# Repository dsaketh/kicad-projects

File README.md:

# KiCad PCB Projects

This repository contains my PCB design projects created using KiCad.

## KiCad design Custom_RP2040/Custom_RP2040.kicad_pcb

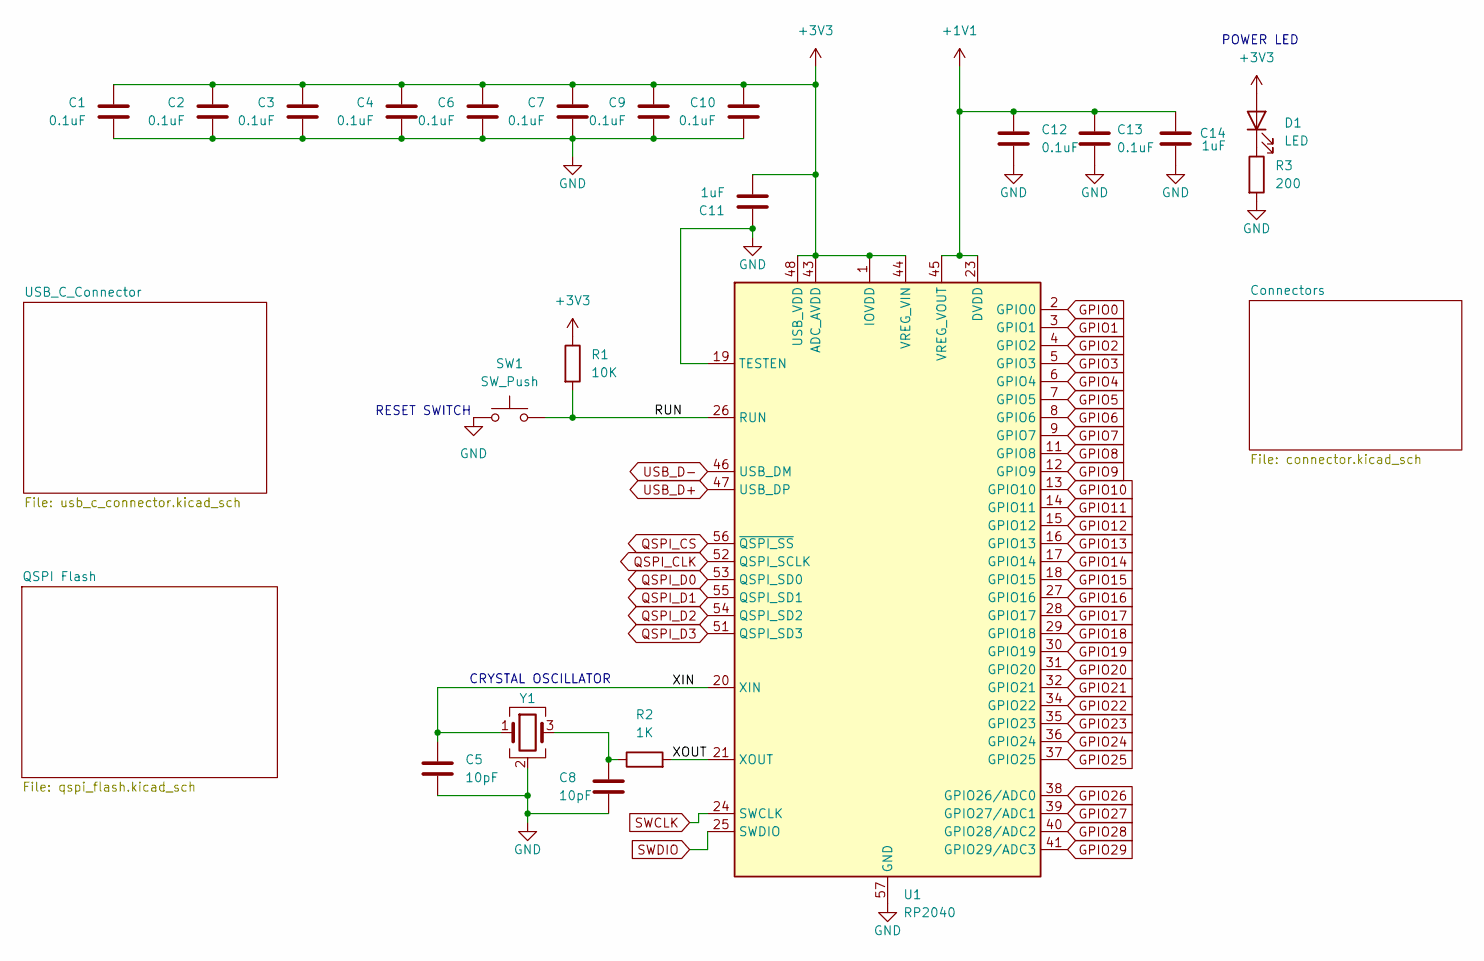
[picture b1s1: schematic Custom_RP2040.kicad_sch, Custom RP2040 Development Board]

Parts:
C1: 0.1uF; C_0603_1608Metric_Pad1.08x0.95mm_HandSolder
C2, C3, C4, C6, C7, C9, C10, C12, C13: 0.1uF; C_0603_1608Metric
C5, C8: 10pF; C_0603_1608Metric
C11, C14: 1uF; C_0603_1608Metric
D1: LED; LED_0603_1608Metric_Pad1.05x0.95mm_HandSolder
R1: 10K; R_0603_1608Metric
R2: 1K; R_0603_1608Metric
R3: 200; R_0603_1608Metric_Pad0.98x0.95mm_HandSolder
SW1: SW_Push; SW_SPST_PTS810
U1: RP2040; QFN-56-1EP_7x7mm_P0.4mm_EP3.2x3.2mm
Y1: Crystal_GND24; Oscillator_SMD_Abracon_ASE-4Pin_3.2x2.5mm

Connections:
+1V1: C12.1, C13.1, C14.2, U1.23 (DVDD), U1.45 (VREG_VOUT), U1.50 (DVDD)
+3V3: C1.1, C2.1, C3.1, C4.1, C6.1, C7.1, C9.1, C10.1, C11.1, D1.2 (A), R1.1, U1.1 (IOVDD), U1.10 (IOVDD), U1.22 (IOVDD), U1.33 (IOVDD), U1.42 (IOVDD), U1.43 (ADC_AVDD), U1.44 (VREG_VIN), U1.48 (USB_VDD), U1.49 (IOVDD); also elsewhere on the board
/RUN: R1.2, SW1.2, U1.26 (RUN)
/XIN: C5.1, U1.20 (XIN), Y1.1
/XOUT: R2.2, U1.21 (XOUT)
GND: C1.2, C2.2, C3.2, C4.2, C5.2, C6.2, C7.2, C8.2, C9.2, C10.2, C11.2, C12.2, C13.2, C14.1, R3.2, SW1.1, U1.19 (TESTEN), U1.57 (GND), Y1.2 (G), Y1.4 (G); also elsewhere on the board
GPIO0: U1.2 (GPIO0); also elsewhere on the board
GPIO1: U1.3 (GPIO1); also elsewhere on the board
GPIO2: U1.4 (GPIO2); also elsewhere on the board
GPIO3: U1.5 (GPIO3); also elsewhere on the board
GPIO4: U1.6 (GPIO4); also elsewhere on the board
GPIO5: U1.7 (GPIO5); also elsewhere on the board
GPIO6: U1.8 (GPIO6); also elsewhere on the board
GPIO7: U1.9 (GPIO7); also elsewhere on the board
GPIO8: U1.11 (GPIO8); also elsewhere on the board
GPIO9: U1.12 (GPIO9); also elsewhere on the board
GPIO10: U1.13 (GPIO10); also elsewhere on the board
GPIO11: U1.14 (GPIO11); also elsewhere on the board
GPIO12: U1.15 (GPIO12); also elsewhere on the board
GPIO13: U1.16 (GPIO13); also elsewhere on the board
GPIO14: U1.17 (GPIO14); also elsewhere on the board
GPIO15: U1.18 (GPIO15); also elsewhere on the board
GPIO16: U1.27 (GPIO16); also elsewhere on the board
GPIO17: U1.28 (GPIO17); also elsewhere on the board
GPIO18: U1.29 (GPIO18); also elsewhere on the board
GPIO19: U1.30 (GPIO19); also elsewhere on the board
GPIO20: U1.31 (GPIO20); also elsewhere on the board
GPIO21: U1.32 (GPIO21); also elsewhere on the board
GPIO22: U1.34 (GPIO22); also elsewhere on the board
GPIO23: U1.35 (GPIO23); also elsewhere on the board
GPIO24: U1.36 (GPIO24); also elsewhere on the board
GPIO25: U1.37 (GPIO25); also elsewhere on the board
GPIO26: U1.38 (GPIO26/ADC0); also elsewhere on the board
GPIO27: U1.39 (GPIO27/ADC1); also elsewhere on the board
GPIO28: U1.40 (GPIO28/ADC2); also elsewhere on the board
GPIO29: U1.41 (GPIO29/ADC3); also elsewhere on the board
unnamed: C8.1, R2.1, Y1.3
unnamed: D1.1 (K), R3.1
QSPI_CLK: U1.52 (QSPI_SCLK); also elsewhere on the board
QSPI_CS: U1.56 (~QSPI_SS); also elsewhere on the board
QSPI_D0: U1.53 (QSPI_SD0); also elsewhere on the board
QSPI_D1: U1.55 (QSPI_SD1); also elsewhere on the board
QSPI_D2: U1.54 (QSPI_SD2); also elsewhere on the board
QSPI_D3: U1.51 (QSPI_SD3); also elsewhere on the board
SWCLK: U1.24 (SWCLK); also elsewhere on the board
SWDIO: U1.25 (SWDIO); also elsewhere on the board
USB_D+: U1.47 (USB_DP); also elsewhere on the board
USB_D-: U1.46 (USB_DM); also elsewhere on the board

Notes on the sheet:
POWER LED
RESET SWITCH
CRYSTAL OSCILLATOR

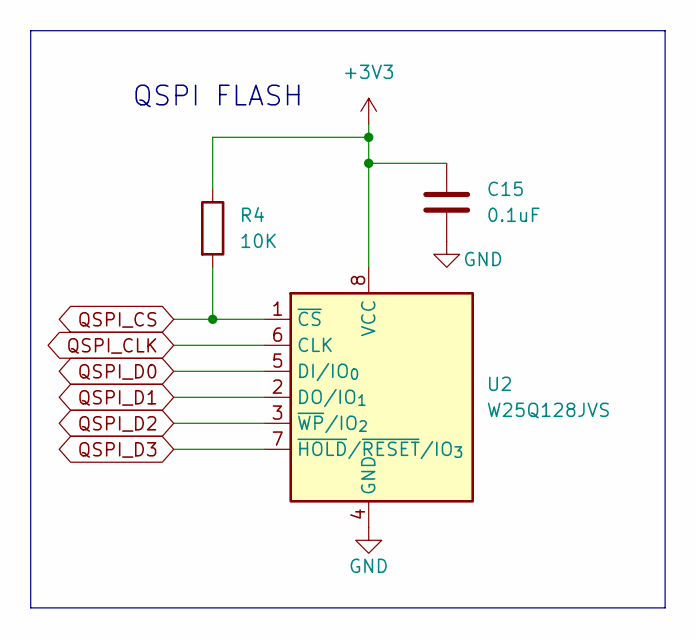
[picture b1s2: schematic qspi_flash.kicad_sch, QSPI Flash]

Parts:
C15: 0.1uF; C_0603_1608Metric
R4: 10K; R_0603_1608Metric
U2: W25Q128JVS; SOIC-8_5.3x5.3mm_P1.27mm

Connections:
+3V3: C15.1, R4.1, U2.8 (VCC); also elsewhere on the board
GND: C15.2, U2.4 (GND); also elsewhere on the board
QSPI_CLK: U2.6 (CLK); also elsewhere on the board
QSPI_CS: R4.2, U2.1 (~CS); also elsewhere on the board
QSPI_D0: U2.5 (DI/IO_{0}); also elsewhere on the board
QSPI_D1: U2.2 (DO/IO_{1}); also elsewhere on the board
QSPI_D2: U2.3 (~WP/IO_{2}); also elsewhere on the board
QSPI_D3: U2.7 (~HOLD/~RESET/IO_{3}); also elsewhere on the board

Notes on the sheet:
QSPI FLASH

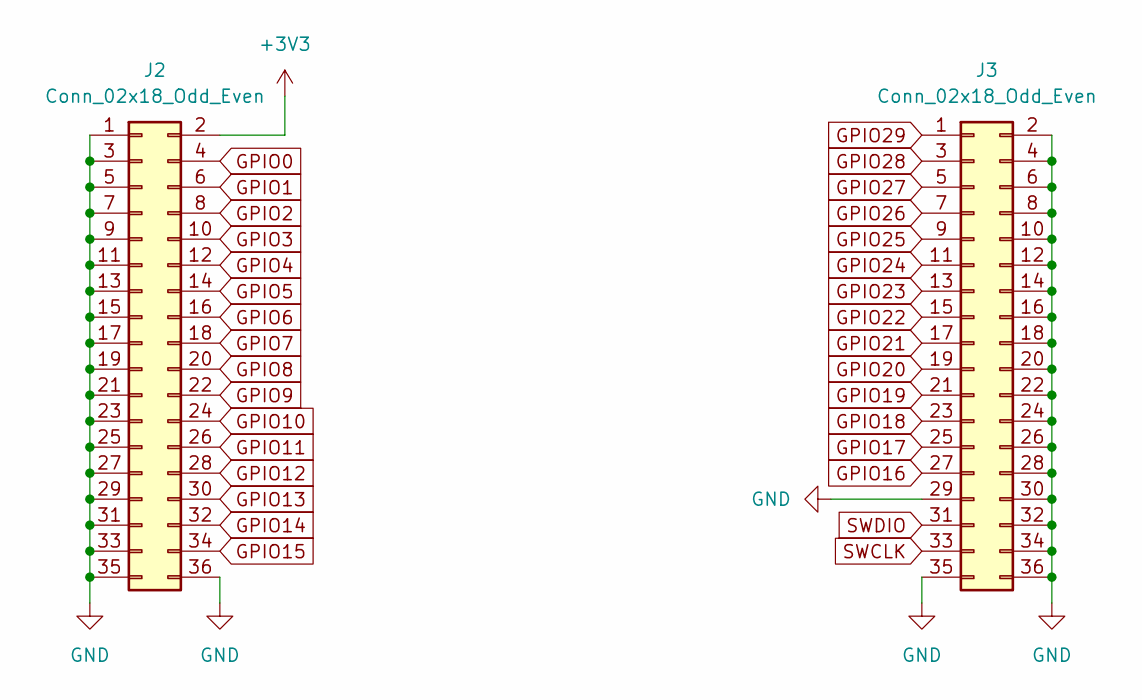
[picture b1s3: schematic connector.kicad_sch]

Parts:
J2, J3: Conn_02x18_Odd_Even; PinHeader_2x18_P2.54mm_Vertical

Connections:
+3V3: J2.2; also elsewhere on the board
GND: J2.1, J2.3, J2.5, J2.7, J2.9, J2.11, J2.13, J2.15, J2.17, J2.19, J2.21, J2.23, J2.25, J2.27, J2.29, J2.31, J2.33, J2.35, J2.36, J3.2, J3.4, J3.6, J3.8, J3.10, J3.12, J3.14, J3.16, J3.18, J3.20, J3.22, J3.24, J3.26, J3.28, J3.29, J3.30, J3.32, J3.34, J3.35, J3.36; also elsewhere on the board
GPIO0: J2.4; also elsewhere on the board
GPIO1: J2.6; also elsewhere on the board
GPIO2: J2.8; also elsewhere on the board
GPIO3: J2.10; also elsewhere on the board
GPIO4: J2.12; also elsewhere on the board
GPIO5: J2.14; also elsewhere on the board
GPIO6: J2.16; also elsewhere on the board
GPIO7: J2.18; also elsewhere on the board
GPIO8: J2.20; also elsewhere on the board
GPIO9: J2.22; also elsewhere on the board
GPIO10: J2.24; also elsewhere on the board
GPIO11: J2.26; also elsewhere on the board
GPIO12: J2.28; also elsewhere on the board
GPIO13: J2.30; also elsewhere on the board
GPIO14: J2.32; also elsewhere on the board
GPIO15: J2.34; also elsewhere on the board
GPIO16: J3.27; also elsewhere on the board
GPIO17: J3.25; also elsewhere on the board
GPIO18: J3.23; also elsewhere on the board
GPIO19: J3.21; also elsewhere on the board
GPIO20: J3.19; also elsewhere on the board
GPIO21: J3.17; also elsewhere on the board
GPIO22: J3.15; also elsewhere on the board
GPIO23: J3.13; also elsewhere on the board
GPIO24: J3.11; also elsewhere on the board
GPIO25: J3.9; also elsewhere on the board
GPIO26: J3.7; also elsewhere on the board
GPIO27: J3.5; also elsewhere on the board
GPIO28: J3.3; also elsewhere on the board
GPIO29: J3.1; also elsewhere on the board
SWCLK: J3.33; also elsewhere on the board
SWDIO: J3.31; also elsewhere on the board

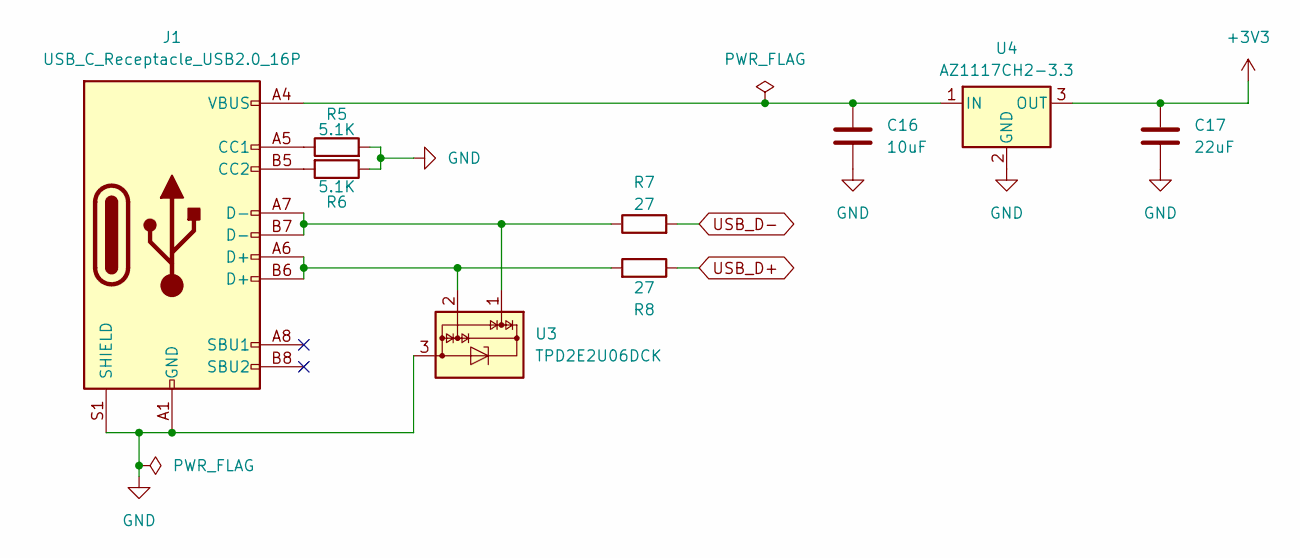
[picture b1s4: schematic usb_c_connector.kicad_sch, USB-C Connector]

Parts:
C16: 10uF; C_0603_1608Metric
C17: 22uF; C_0603_1608Metric
J1: USB_C_Receptacle_USB2.0_16P; USB_C_Receptacle_G-Switch_GT-USB-7010ASV
R5, R6: 5.1K; R_0603_1608Metric
R7, R8: 27; R_0603_1608Metric
U3: TPD2E2U06DCK; SOT-323_SC-70
U4: AZ1117CH2-3.3; SOT-223-3_TabPin2

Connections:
+3V3: C17.1, U4.3 (OUT); also elsewhere on the board
GND: C16.2, C17.2, J1.A1 (GND), J1.A12 (GND), J1.B1 (GND), J1.B12 (GND), J1.S1 (SHIELD), R5.2, R6.1, U3.3, U4.2 (GND); also elsewhere on the board
unnamed: J1.A5 (CC1), R5.1
unnamed: J1.B5 (CC2), R6.2
unnamed: J1.A6 (D+), J1.B6 (D+), R8.2, U3.2
unnamed: J1.A7 (D-), J1.B7 (D-), R7.1, U3.1
unnamed: C16.1, J1.A4 (VBUS), J1.A9 (VBUS), J1.B4 (VBUS), J1.B9 (VBUS), U4.1 (IN)
USB_D+: R8.1; also elsewhere on the board
USB_D-: R7.2; also elsewhere on the board

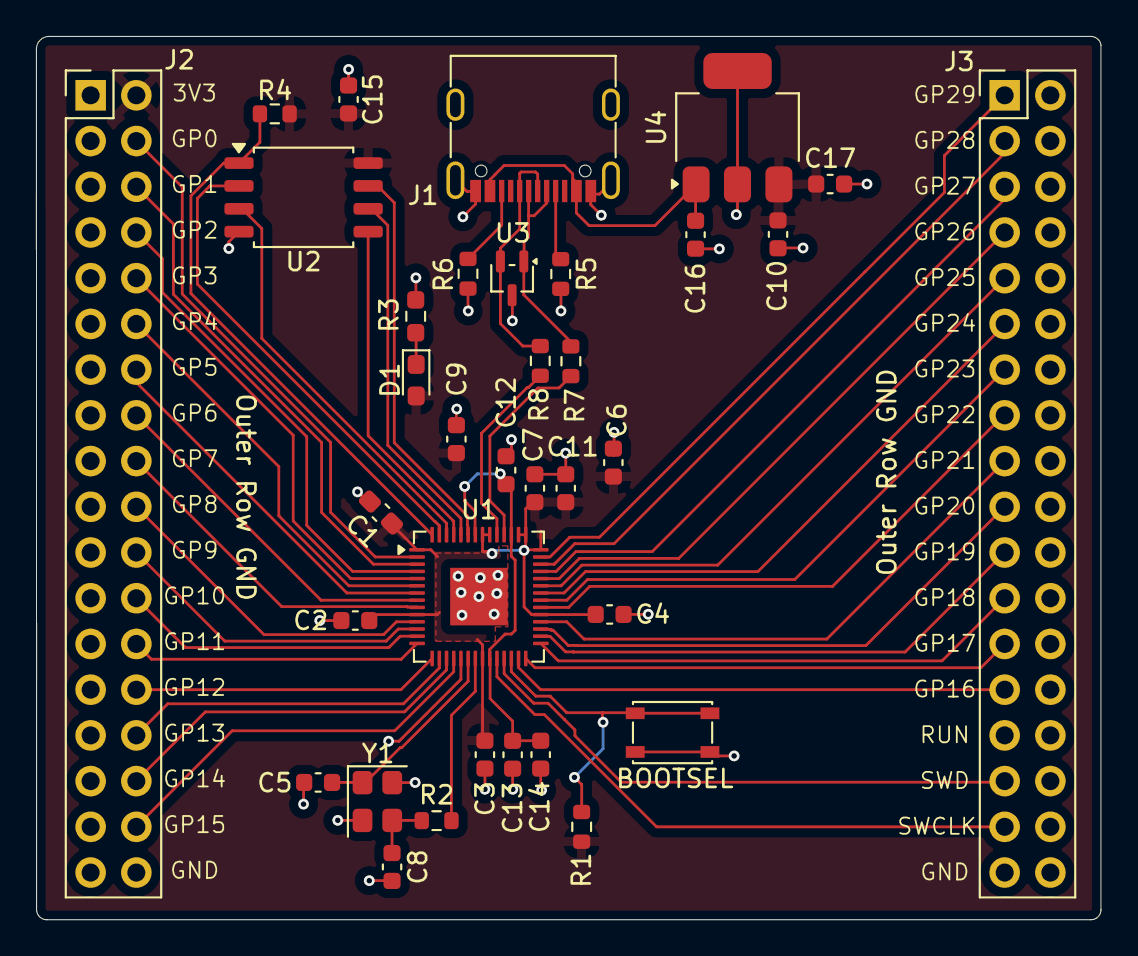
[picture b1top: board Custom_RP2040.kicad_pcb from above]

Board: 2 copper layers, 59.1 x 49.1 mm, 35 parts (0 on the bottom side), 53 nets.

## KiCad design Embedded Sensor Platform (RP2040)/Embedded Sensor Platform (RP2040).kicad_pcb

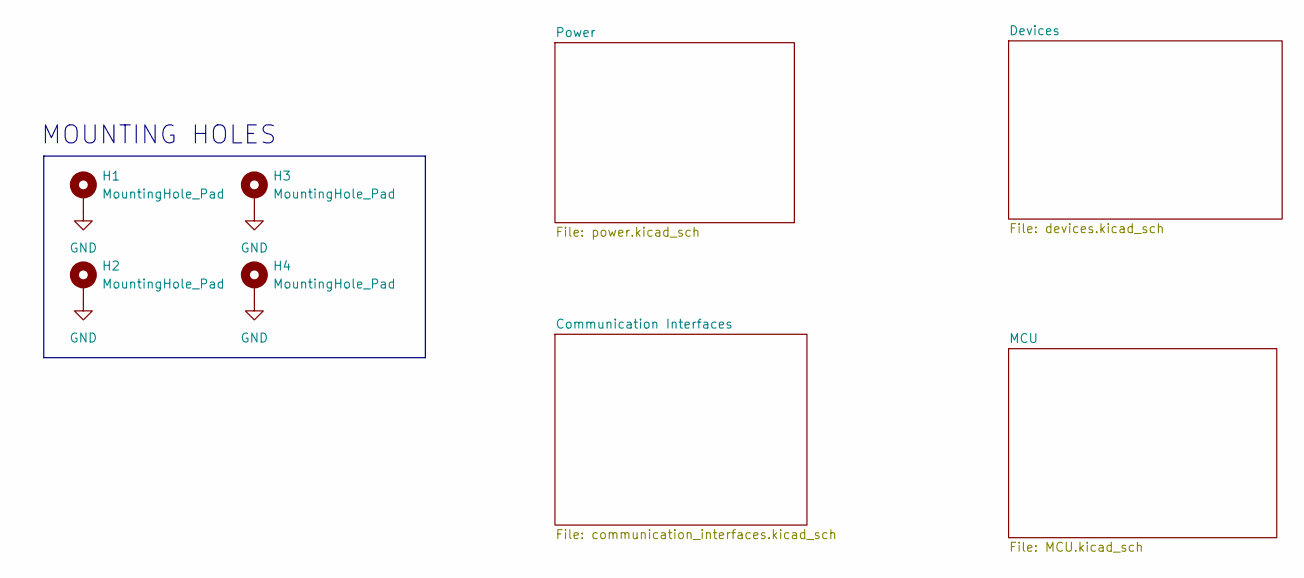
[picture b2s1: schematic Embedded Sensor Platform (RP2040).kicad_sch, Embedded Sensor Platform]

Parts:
H1, H2, H3, H4: MountingHole_Pad; MountingHole_2.2mm_M2_Pad

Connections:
GND: H1.1, H2.1, H3.1, H4.1; also elsewhere on the board

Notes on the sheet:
MOUNTING HOLES

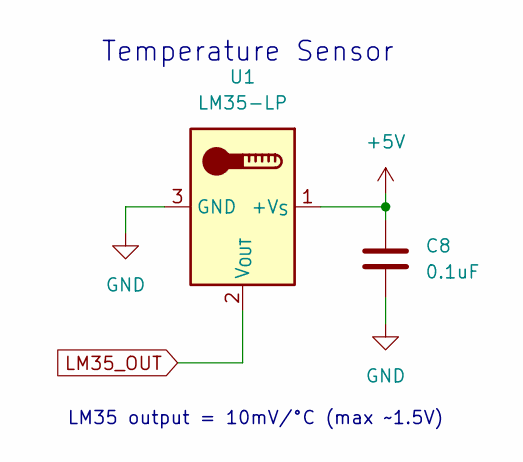
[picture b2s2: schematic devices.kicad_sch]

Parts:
C8: 0.1uF; C_0603_1608Metric_Pad1.08x0.95mm_HandSolder
U1: LM35-LP; TO-92_Inline

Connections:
+5V: C8.1, U1.1 (+V_{S}); also elsewhere on the board
GND: C8.2, U1.3 (GND); also elsewhere on the board
LM35_OUT: U1.2 (V_{OUT}); also elsewhere on the board

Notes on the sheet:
Temperature Sensor
LM35 output = 10mV/°C (max ~1.5V)

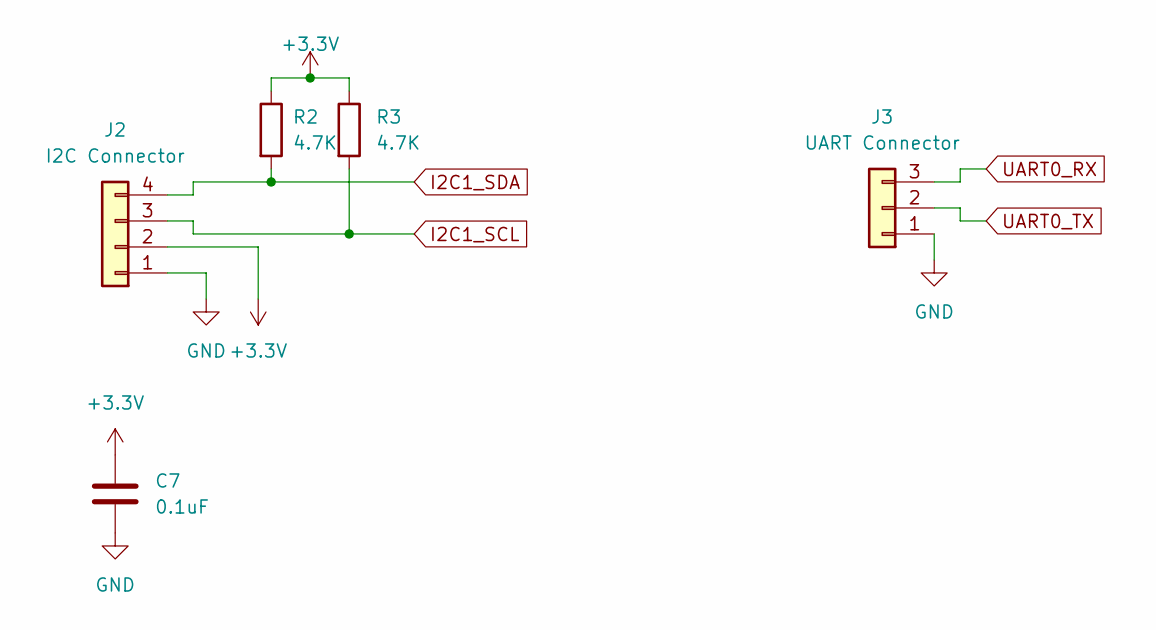
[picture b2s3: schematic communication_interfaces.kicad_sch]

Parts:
C7: 0.1uF; C_0603_1608Metric_Pad1.08x0.95mm_HandSolder
J2: I2C Connector; PinSocket_1x04_P2.00mm_Vertical
J3: UART Connector; PinSocket_1x03_P2.00mm_Vertical
R2, R3: 4.7K; R_0603_1608Metric_Pad0.98x0.95mm_HandSolder

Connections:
+3.3V: C7.1, J2.2, R2.1, R3.1; also elsewhere on the board
GND: C7.2, J2.1, J3.1; also elsewhere on the board
I2C1_SCL: J2.3, R3.2; also elsewhere on the board
I2C1_SDA: J2.4, R2.2; also elsewhere on the board
UART0_RX: J3.3; also elsewhere on the board
UART0_TX: J3.2; also elsewhere on the board

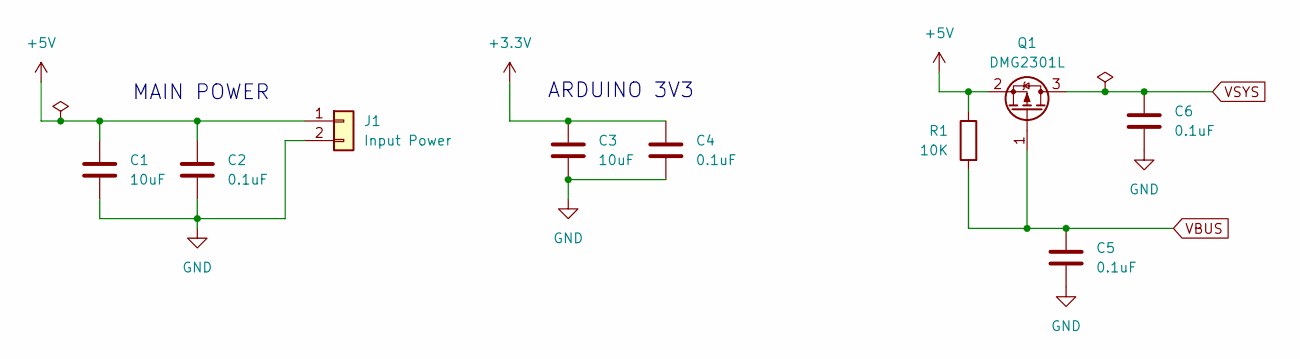
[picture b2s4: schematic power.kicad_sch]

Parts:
C1, C3: 10uF; C_0603_1608Metric_Pad1.08x0.95mm_HandSolder
C2, C4, C5, C6: 0.1uF; C_0603_1608Metric_Pad1.08x0.95mm_HandSolder
J1: Input Power; PinHeader_1x02_P2.00mm_Vertical
Q1: DMG2301L; SOT-23
R1: 10K; R_0603_1608Metric_Pad0.98x0.95mm_HandSolder

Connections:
+3.3V: C3.1, C4.1; also elsewhere on the board
+5V: C1.1, C2.1, J1.1, Q1.2 (S), R1.1; also elsewhere on the board
GND: C1.2, C2.2, C3.2, C4.2, C5.2, C6.2, J1.2; also elsewhere on the board
VBUS: C5.1, Q1.1 (G), R1.2; also elsewhere on the board
VSYS: C6.1, Q1.3 (D); also elsewhere on the board

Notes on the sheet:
ARDUINO 3V3
MAIN POWER

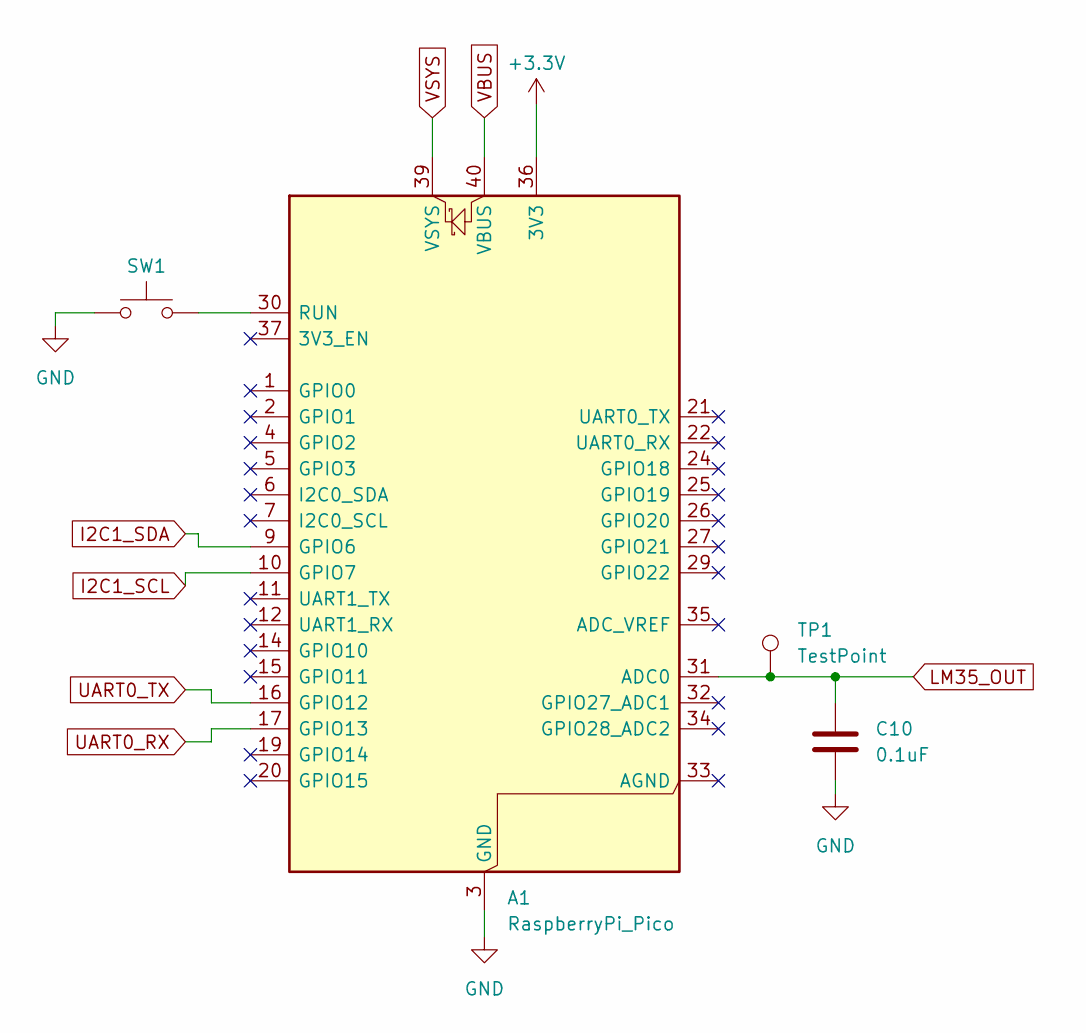
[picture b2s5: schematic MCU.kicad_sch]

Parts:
A1: RaspberryPi_Pico; RaspberryPi_Pico_Common_THT
C10: 0.1uF; C_0603_1608Metric_Pad1.08x0.95mm_HandSolder
SW1: SW_Push; SW_SPST_PTS810
TP1: TestPoint; TestPoint_THTPad_D2.0mm_Drill1.0mm

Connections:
+3.3V: A1.36 (3V3); also elsewhere on the board
GND: A1.3 (GND), A1.8 (GND), A1.13 (GND), A1.18 (GND), A1.23 (GND), A1.28 (GND), A1.38 (GND), C10.2, SW1.1; also elsewhere on the board
I2C1_SCL: A1.10 (GPIO7); also elsewhere on the board
I2C1_SDA: A1.9 (GPIO6); also elsewhere on the board
LM35_OUT: A1.31 (ADC0), C10.1, TP1.1; also elsewhere on the board
unnamed: A1.30 (RUN), SW1.2
UART0_RX: A1.17 (GPIO13); also elsewhere on the board
UART0_TX: A1.16 (GPIO12); also elsewhere on the board
VBUS: A1.40 (VBUS); also elsewhere on the board
VSYS: A1.39 (VSYS); also elsewhere on the board

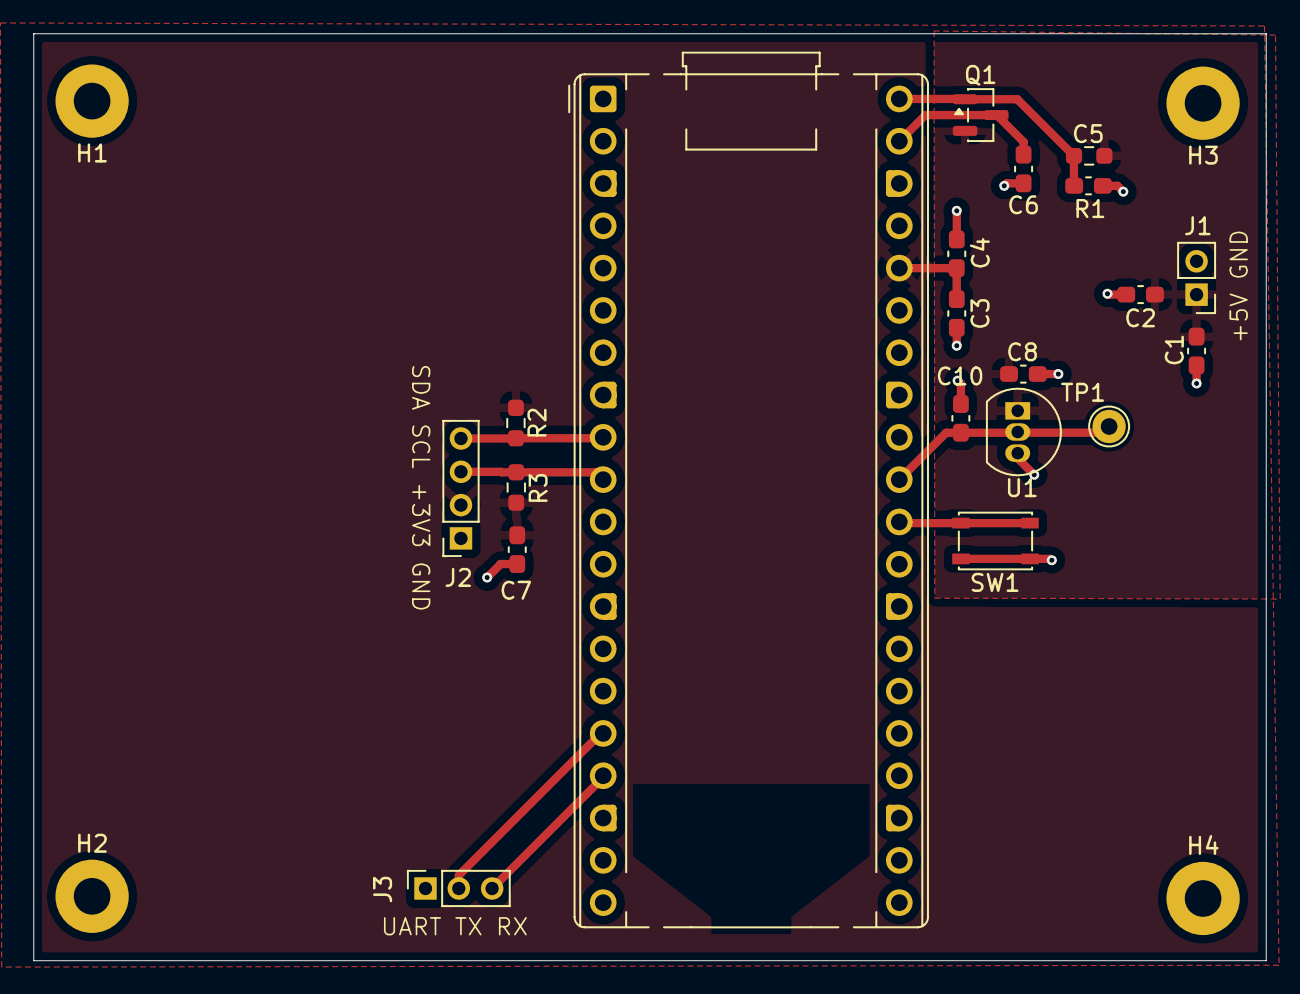
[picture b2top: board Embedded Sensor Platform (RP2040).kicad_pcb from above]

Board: 2 copper layers, 74.0 x 55.7 mm, 24 parts (0 on the bottom side), 11 nets.

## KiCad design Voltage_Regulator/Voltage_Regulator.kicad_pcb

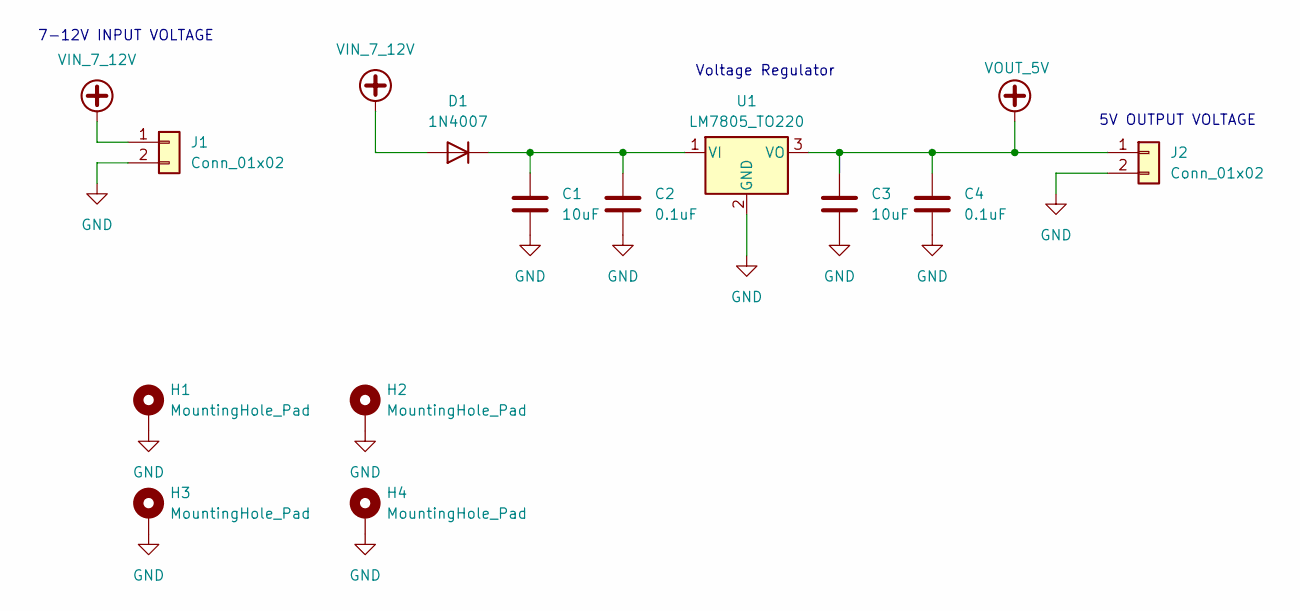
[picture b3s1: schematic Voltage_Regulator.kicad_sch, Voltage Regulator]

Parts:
C1, C3: 10uF; C_0603_1608Metric
C2, C4: 0.1uF; C_0603_1608Metric
D1: 1N4007; D_DO-41_SOD81_P10.16mm_Horizontal
H1, H2, H3, H4: MountingHole_Pad; MountingHole_2.2mm_M2_Pad
J1, J2: Conn_01x02; PinHeader_1x02_P1.00mm_Vertical
U1: LM7805_TO220; TO-220-3_Vertical

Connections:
GND: C1.2, C2.2, C3.2, C4.2, H1.1, H2.1, H3.1, H4.1, J1.2, J2.2, U1.2 (GND)
unnamed: C1.1, C2.1, D1.1 (K), U1.1 (VI)
VIN_7_12V: D1.2 (A), J1.1
VOUT_5V: C3.1, C4.1, J2.1, U1.3 (VO)

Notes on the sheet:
5V OUTPUT VOLTAGE
Voltage Regulator
7-12V INPUT VOLTAGE

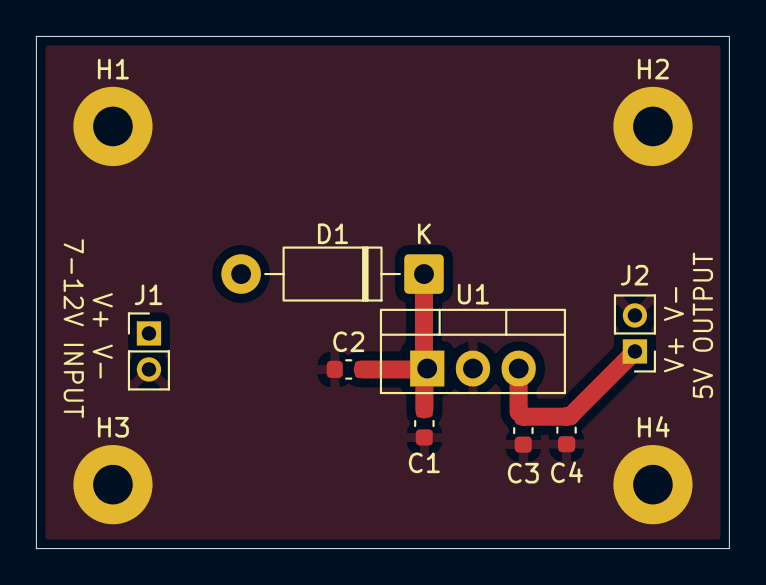
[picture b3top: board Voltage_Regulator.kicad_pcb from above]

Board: 2 copper layers, 38.5 x 28.5 mm, 12 parts (0 on the bottom side), 4 nets.

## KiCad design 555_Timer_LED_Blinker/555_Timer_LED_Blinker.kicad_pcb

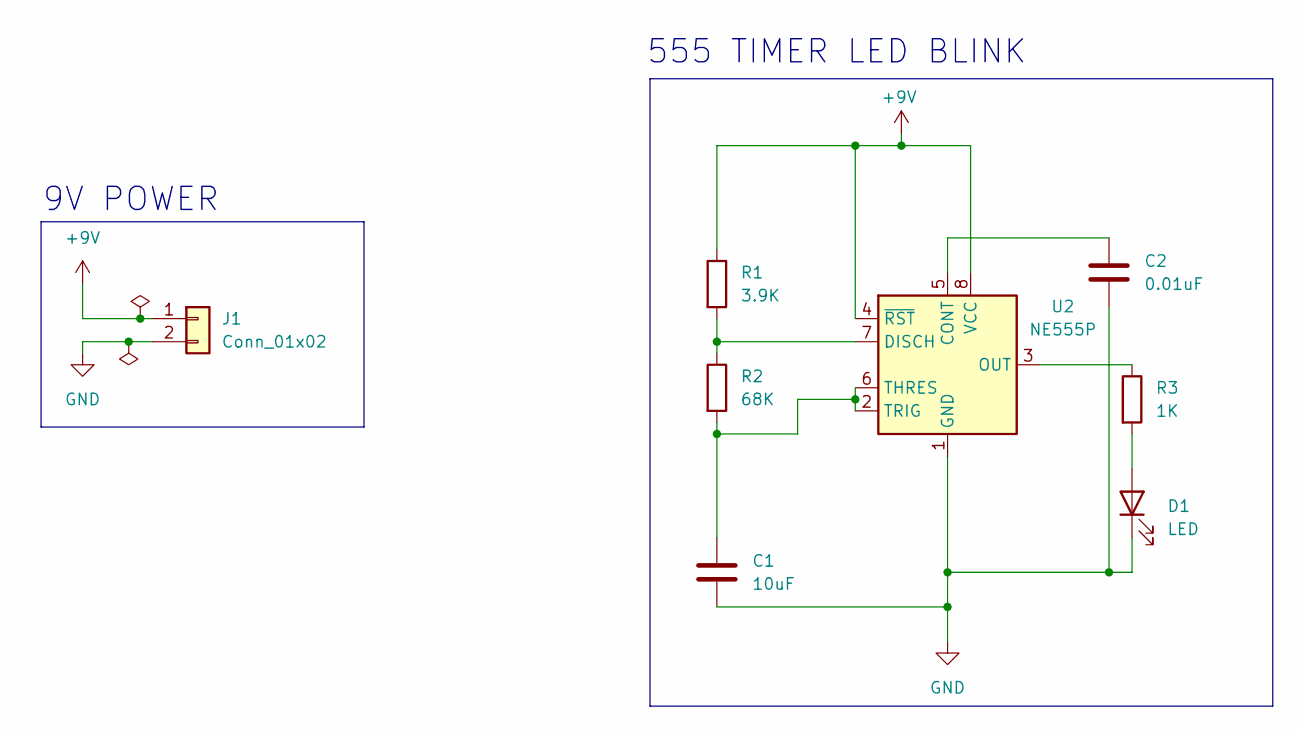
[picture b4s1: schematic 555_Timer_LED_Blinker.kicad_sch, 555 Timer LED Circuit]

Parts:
C1: 10uF; C_0603_1608Metric
C2: 0.01uF; C_0603_1608Metric
D1: LED; LED_D5.0mm
J1: Conn_01x02; PinHeader_1x02_P2.00mm_Vertical
R1: 3.9K; R_0603_1608Metric
R2: 68K; R_0603_1608Metric
R3: 1K; R_0603_1608Metric
U2: NE555P; DIP-8_W7.62mm

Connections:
+9V: J1.1, R1.1, U2.4 (~RST), U2.8 (VCC)
GND: C1.2, C2.2, D1.1 (K), J1.2, U2.1 (GND)
unnamed: D1.2 (A), R3.2
unnamed: C2.1, U2.5 (CONT)
unnamed: R1.2, R2.1, U2.7 (DISCH)
unnamed: R3.1, U2.3 (OUT)
unnamed: C1.1, R2.2, U2.2 (TRIG), U2.6 (THRES)

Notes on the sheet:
555 TIMER LED BLINK
9V POWER

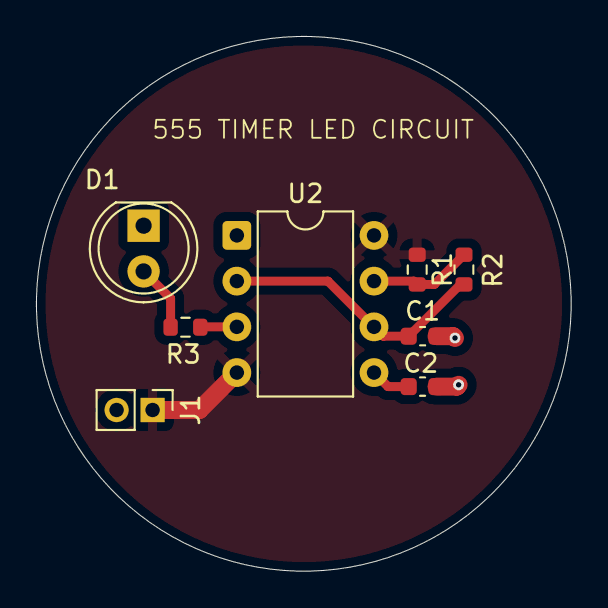
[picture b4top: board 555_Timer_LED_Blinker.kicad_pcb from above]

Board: 2 copper layers, 29.7 x 29.7 mm, 8 parts (0 on the bottom side), 7 nets.

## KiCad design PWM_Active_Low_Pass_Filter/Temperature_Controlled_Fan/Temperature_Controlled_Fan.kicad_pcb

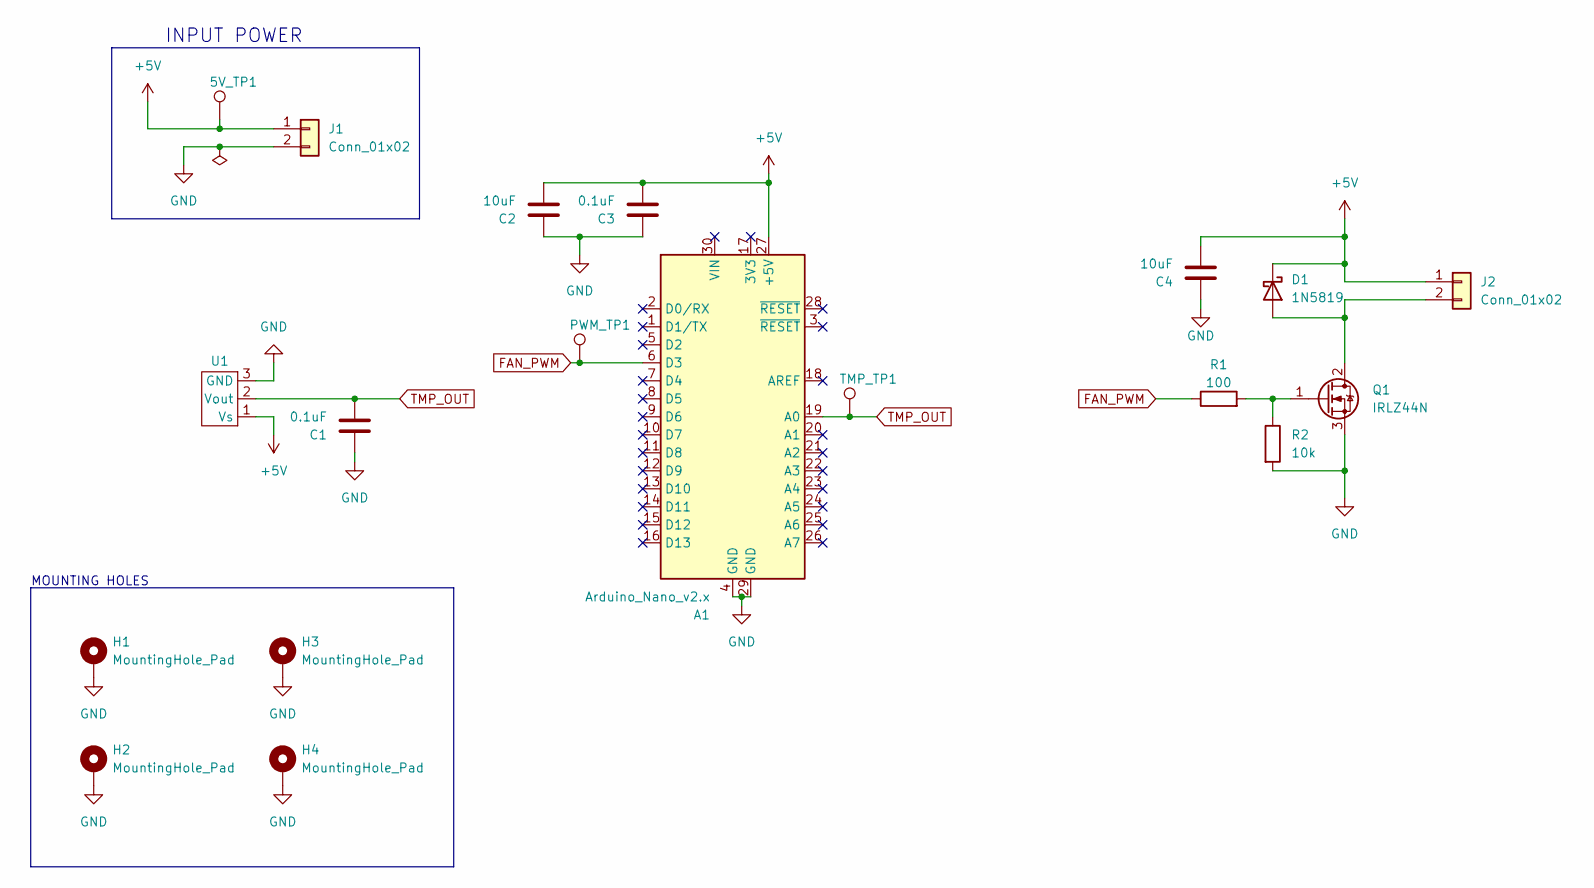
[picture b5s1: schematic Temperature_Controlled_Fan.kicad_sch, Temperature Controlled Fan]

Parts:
5V_TP1: TestPoint; TestPoint_Plated_Hole_D2.0mm
A1: Arduino_Nano_v2.x; Arduino_Nano
C1, C3: 0.1uF; C_0603_1608Metric
C2, C4: 10uF; C_0603_1608Metric
D1: 1N5819; D_DO-41_SOD81_P10.16mm_Horizontal
H1, H2, H3, H4: MountingHole_Pad; MountingHole_2.5mm_Pad
J1, J2: Conn_01x02; PinHeader_1x02_P2.00mm_Vertical
PWM_TP1: TestPoint; TestPoint_Plated_Hole_D2.0mm
Q1: IRLZ44N; TO-220-3_Vertical
R1: 100; R_0603_1608Metric
R2: 10k; R_0603_1608Metric
TMP_TP1: TestPoint; TestPoint_Plated_Hole_D2.0mm
U1: TO-92

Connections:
+5V: 5V_TP1.1, A1.27 (+5V), C2.2, C3.2, C4.2, D1.1 (K), J1.1, J2.1, U1.1 (Vs)
FAN_PWM: A1.6 (D3), PWM_TP1.1, R1.1
GND: A1.4 (GND), A1.29 (GND), C1.1, C2.1, C3.1, C4.1, H1.1, H2.1, H3.1, H4.1, J1.2, Q1.3 (S), R2.2, U1.3 (GND)
unnamed: D1.2 (A), J2.2, Q1.2 (D)
unnamed: Q1.1 (G), R1.2, R2.1
TMP_OUT: A1.19 (A0), C1.2, TMP_TP1.1, U1.2 (Vout)

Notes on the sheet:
INPUT POWER
MOUNTING HOLES

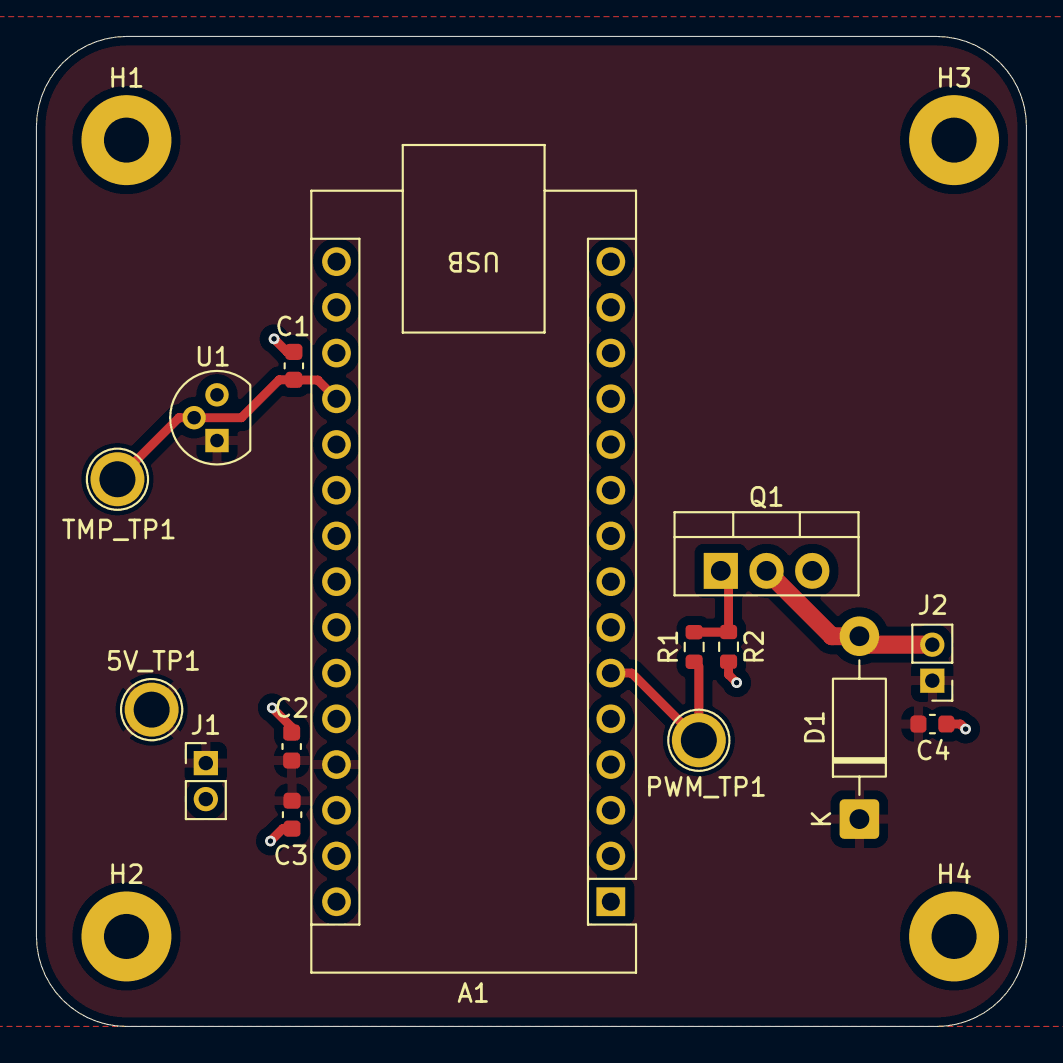
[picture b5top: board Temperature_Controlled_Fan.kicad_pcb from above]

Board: 2 copper layers, 55.0 x 55.0 mm, 19 parts (0 on the bottom side), 6 nets.

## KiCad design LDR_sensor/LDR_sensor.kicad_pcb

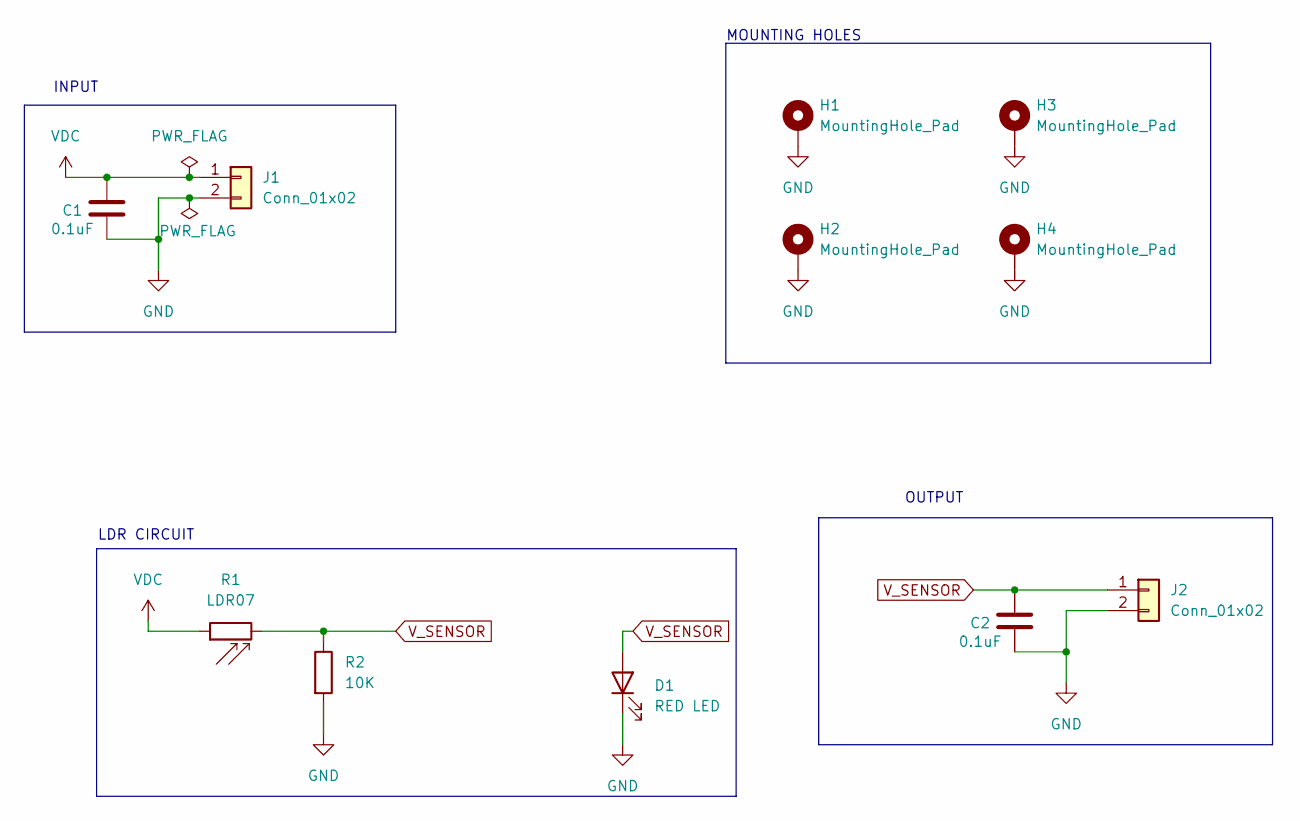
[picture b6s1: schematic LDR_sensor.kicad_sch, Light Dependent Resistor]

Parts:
C1, C2: 0.1uF; C_0603_1608Metric
D1: RED LED; LED_D3.0mm
H1, H2, H3, H4: MountingHole_Pad; MountingHole_2.5mm_Pad
J1, J2: Conn_01x02; PinHeader_2x01_P2.00mm_Vertical
R1: LDR07; R_LDR_5.1x4.3mm_P3.4mm_Vertical
R2: 10K; R_0603_1608Metric

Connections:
GND: C1.2, C2.2, D1.1 (K), H1.1, H2.1, H3.1, H4.1, J1.2, J2.2, R2.2
VDC: C1.1, J1.1, R1.1
V_SENSOR: C2.1, D1.2 (A), J2.1, R1.2, R2.1

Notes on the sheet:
INPUT
LDR CIRCUIT
MOUNTING HOLES
OUTPUT
